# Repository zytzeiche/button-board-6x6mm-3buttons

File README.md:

# button-board-6x6mm-3buttons

External button board for buttons for Arduino or Raspberry Pi.

- Dimensions: 52 x 12 mm
- Mounting holes: M3 holes (3.2 mm), distance 36 mm
- Buttons: 6x6 mm tactile push buttons

This board can be used for Button pins, which are pulled high or pulled low. If the button pin is pulled low, solder a bridge to VCC for that button.

__Instructions__

- Solder a bridge on the back side of the board for every button. For a pin which is pulled low by default, solder the bridge to GND.

__More PCBs__

- [Button Board with 4 Buttons](https://github.com/zytzeiche/button-board-6x6mm-4buttons)

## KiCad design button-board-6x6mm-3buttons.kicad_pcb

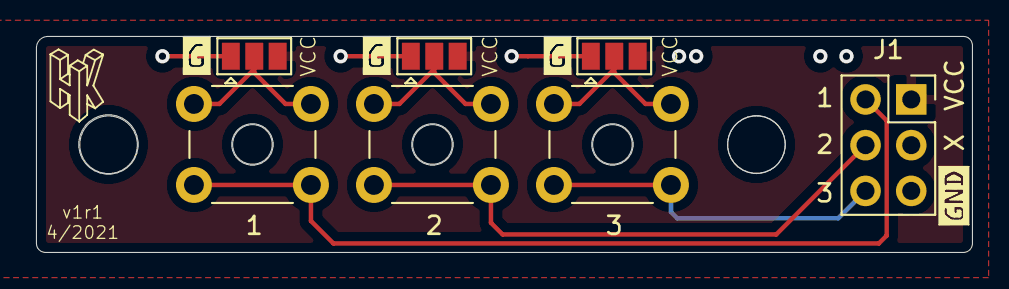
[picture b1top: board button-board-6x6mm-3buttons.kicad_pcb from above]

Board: 2 copper layers, 52.0 x 12.0 mm, 12 parts (0 on the bottom side), 8 nets.

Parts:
H1, H5: MountingHole; MountingHole_3.2mm_M3
H2, H3, H4: MountingHole; MountingHole_2.2mm_M2
J1: Conn_02x03_Counter_Clockwise; PinSocket_2x03_P2.54mm_Vertical
JP1, JP2, JP3: Jumper_3_Open; SolderJumper-3_P1.3mm_Open_Pad1.0x1.5mm
SW1, SW2, SW3: SW_Push; SW_PUSH_6mm_H7.3mm

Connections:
GND: J1.5, JP1.1, JP2.1, JP3.1
unnamed: JP1.2, SW1.1
unnamed: J1.2, SW1.2
unnamed: JP2.2, SW2.1
unnamed: J1.4, SW2.2
unnamed: JP3.2, SW3.1
unnamed: J1.6, SW3.2
VCC: J1.1, JP1.3, JP2.3, JP3.3

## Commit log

2021-05-23 images
2021-06-09 v1r1-printed
2021-06-10 doc updated
